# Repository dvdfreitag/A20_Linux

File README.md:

# A20_Linux
Allwinner A20-powered Linux server

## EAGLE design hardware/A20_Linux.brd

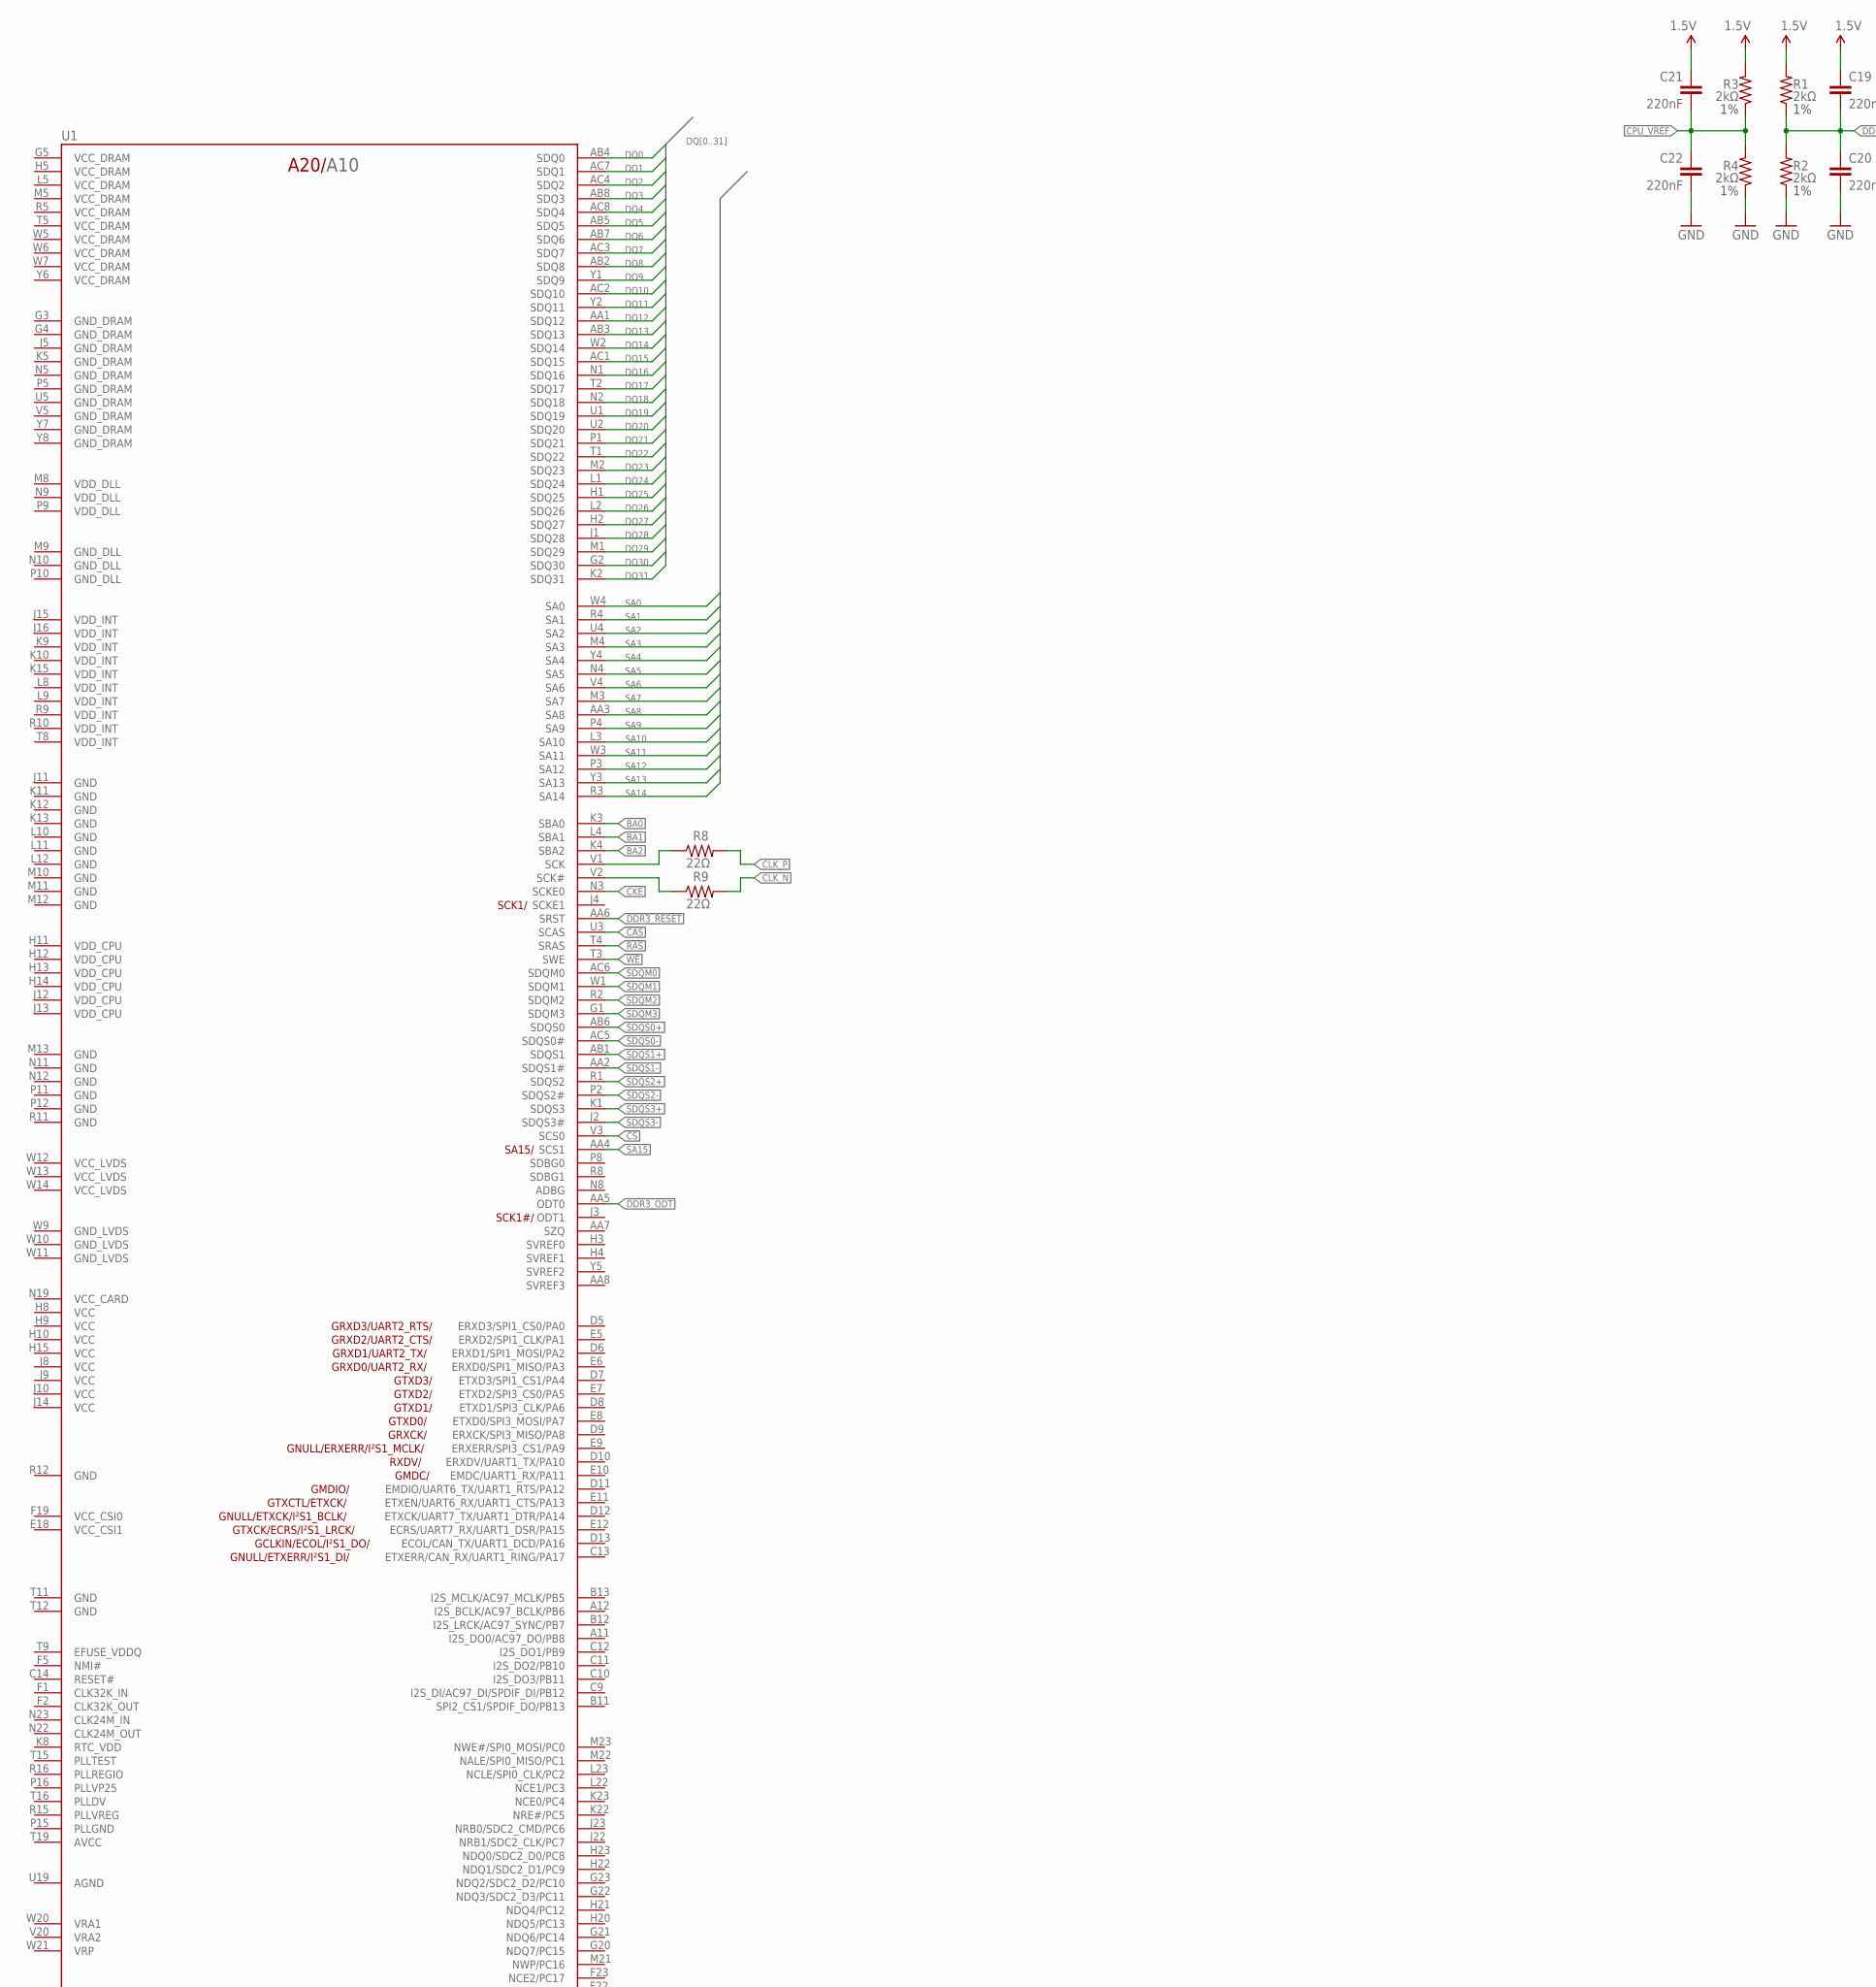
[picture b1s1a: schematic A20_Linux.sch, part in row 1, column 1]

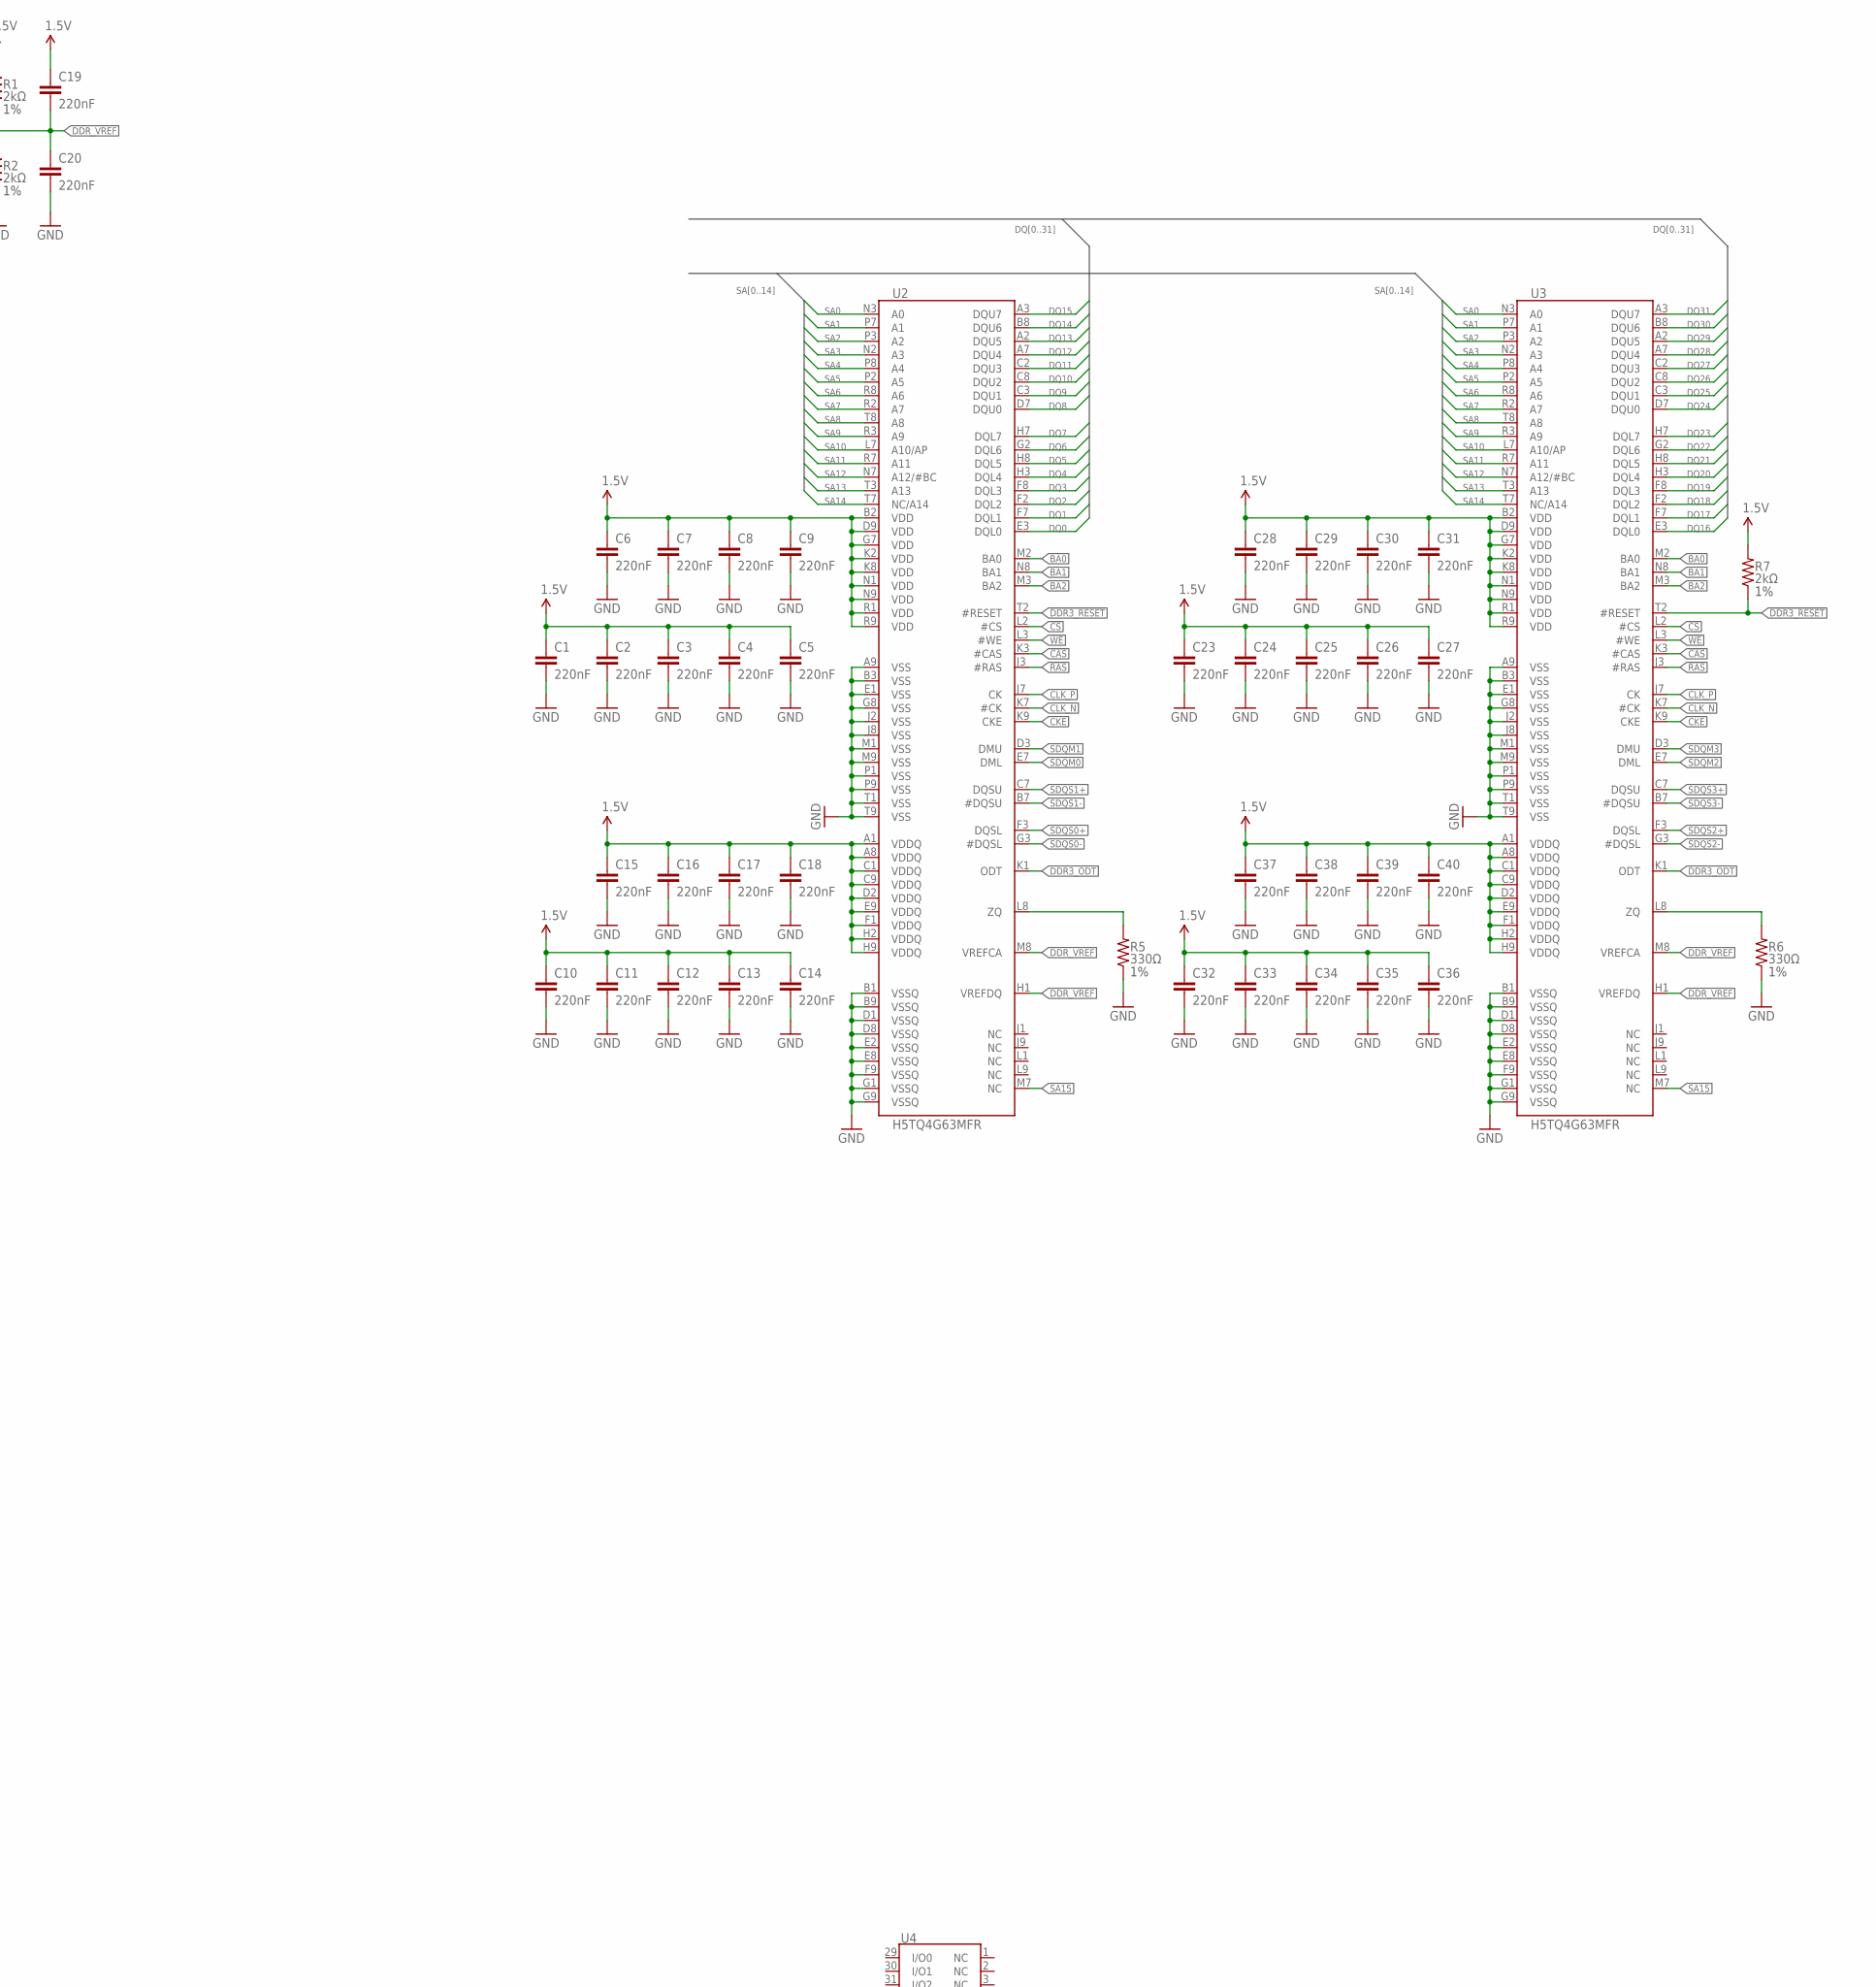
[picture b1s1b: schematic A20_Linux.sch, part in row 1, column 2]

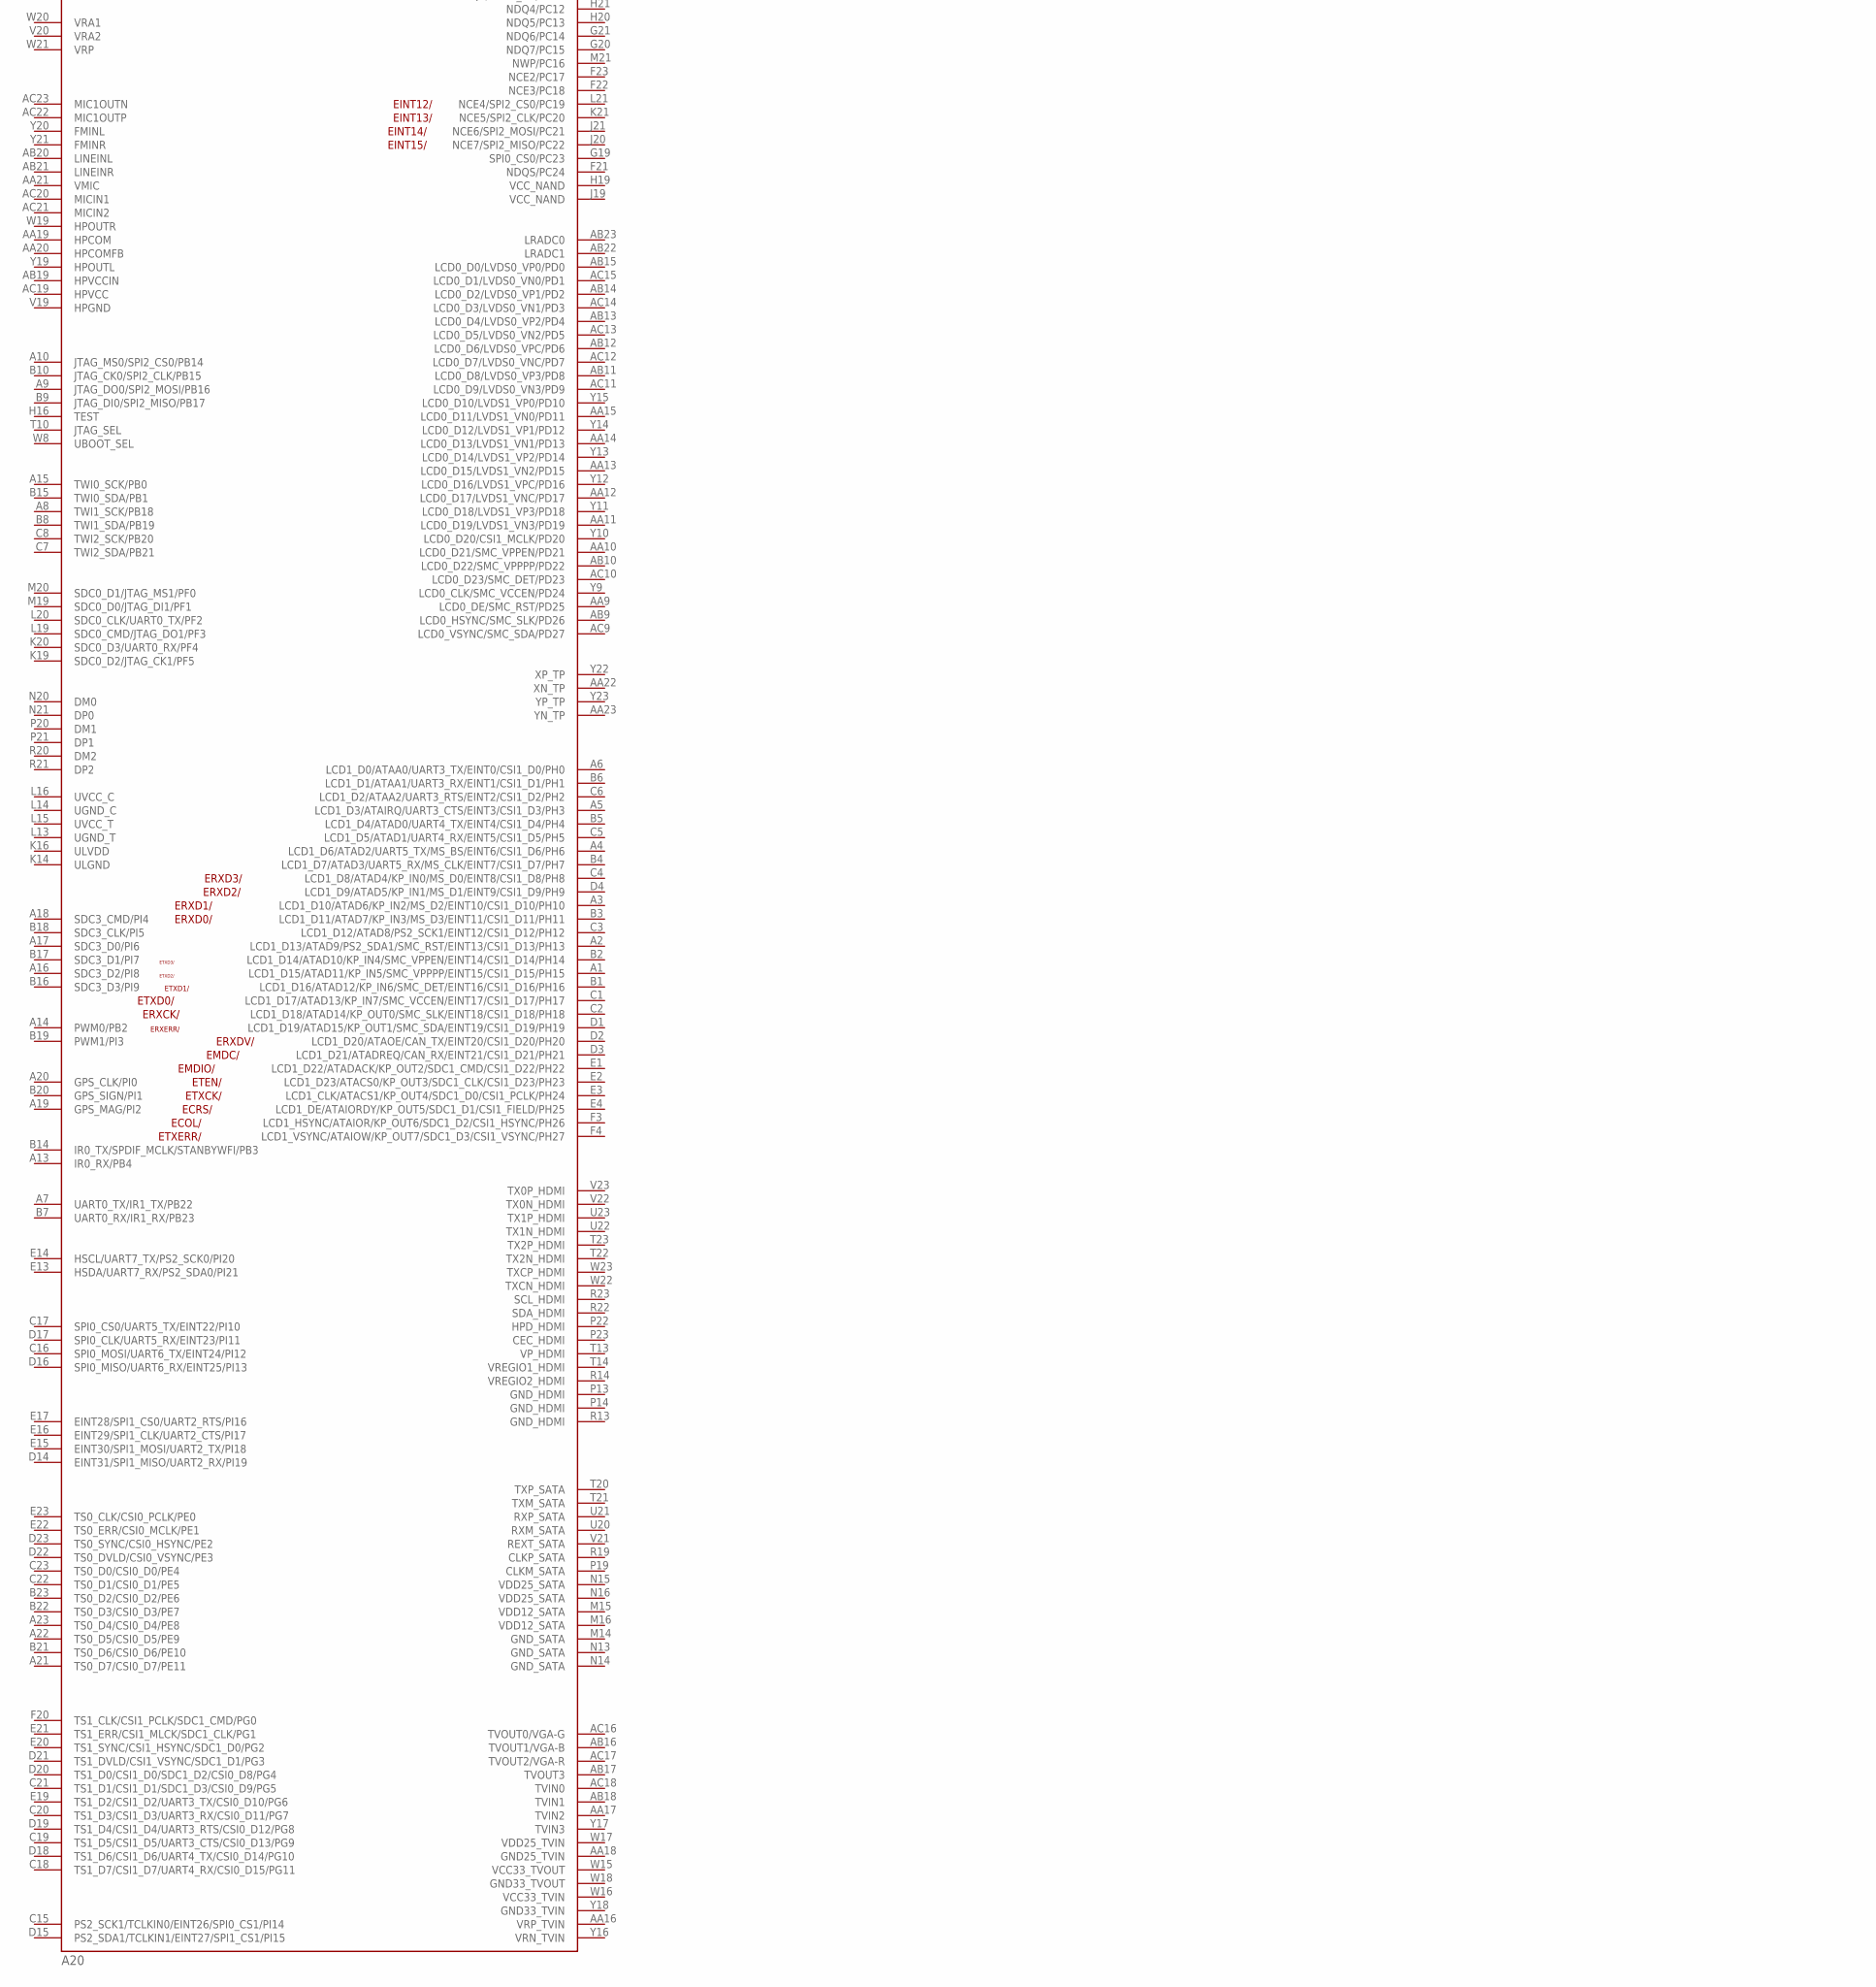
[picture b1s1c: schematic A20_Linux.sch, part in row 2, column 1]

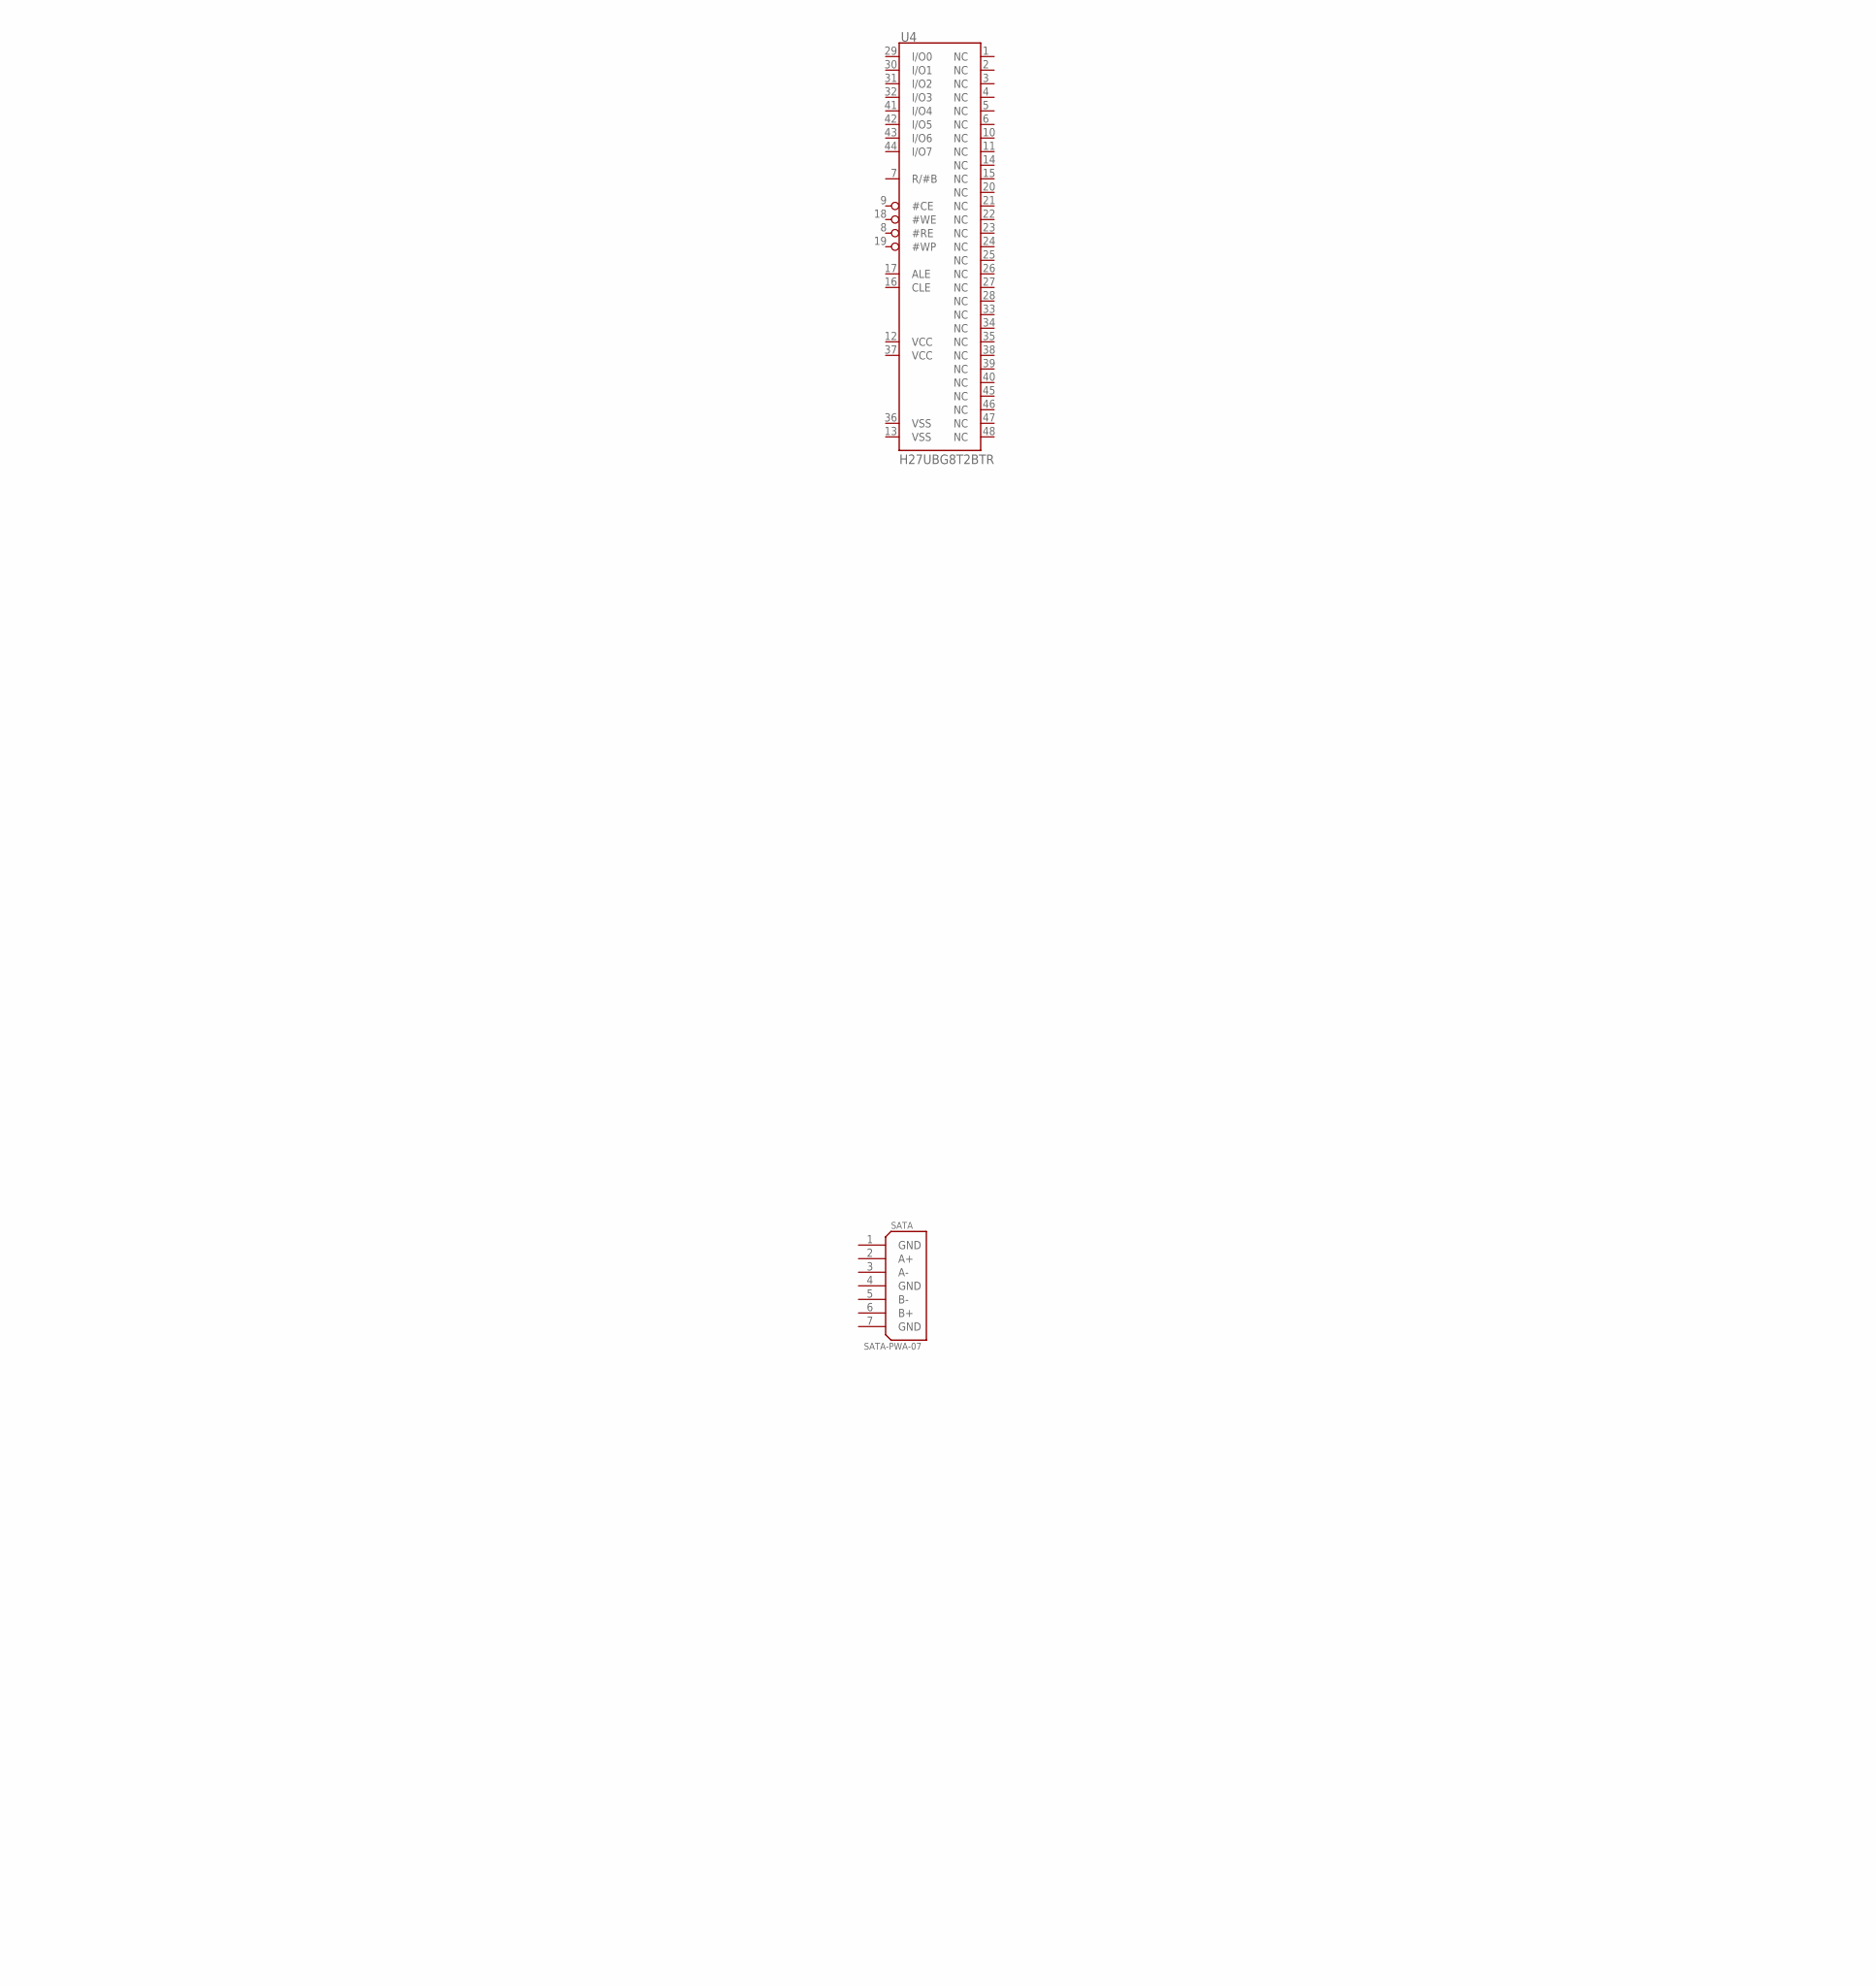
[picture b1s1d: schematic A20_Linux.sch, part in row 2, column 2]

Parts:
C1, C2, C3, C4, C5, C6, C7, C8, C9, C10, C11, C12, C13, C14, C15, C16, C17, C18, C19, C20, C21, C22, C23, C24, C25, C26, C27, C28, C29, C30, C31, C32, C33, C34, C35, C36, C37, C38, C39, C40: 220nF; 0805
R1, R2, R3, R4, R7: 2kΩ; 0805
R5, R6: 330Ω; 0805
R8, R9: 22Ω; 0402-RES
SATA: SATA-PWA-07
U1: A20; TFBGA441
U2, U3: H5TQ4G63MFR; FBGA96_SK
U4: H27UBG8T2BTR; TSOP48

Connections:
1.5V: C1.1, C2.1, C3.1, C4.1, C5.1, C6.1, C7.1, C8.1, C9.1, C10.1, C11.1, C12.1, C13.1, C14.1, C15.1, C16.1, C17.1, C18.1, C19.1, C21.1, C23.1, C24.1, C25.1, C26.1, C27.1, C28.1, C29.1, C30.1, C31.1, C32.1, C33.1, C34.1, C35.1, C36.1, C37.1, C38.1, C39.1, C40.1, R1.2, R3.2, R7.2, U2.A1 (VDDQ), U2.A8 (VDDQ), U2.B2 (VDD), U2.C1 (VDDQ), U2.C9 (VDDQ), U2.D2 (VDDQ), U2.D9 (VDD), U2.E9 (VDDQ), U2.F1 (VDDQ), U2.G7 (VDD), U2.H2 (VDDQ), U2.H9 (VDDQ), U2.K2 (VDD), U2.K8 (VDD), U2.N1 (VDD), U2.N9 (VDD), U2.R1 (VDD), U2.R9 (VDD), U3.A1 (VDDQ), U3.A8 (VDDQ), U3.B2 (VDD), U3.C1 (VDDQ), U3.C9 (VDDQ), U3.D2 (VDDQ), U3.D9 (VDD), U3.E9 (VDDQ), U3.F1 (VDDQ), U3.G7 (VDD), U3.H2 (VDDQ), U3.H9 (VDDQ), U3.K2 (VDD), U3.K8 (VDD), U3.N1 (VDD), U3.N9 (VDD), U3.R1 (VDD), U3.R9 (VDD)
!CAS: U1.U3 (SCAS), U2.K3 (#CAS), U3.K3 (#CAS)
!CS: U1.V3 (SCS0), U2.L2 (#CS), U3.L2 (#CS)
!DDR3_RESET: R7.1, U1.AA6 (SRST), U2.T2 (#RESET), U3.T2 (#RESET)
!RAS: U1.T4 (SRAS), U2.J3 (#RAS), U3.J3 (#RAS)
!WE: U1.T3 (SWE), U2.L3 (#WE), U3.L3 (#WE)
BA0: U1.K3 (SBA0), U2.M2 (BA0), U3.M2 (BA0)
BA1: U1.L4 (SBA1), U2.N8 (BA1), U3.N8 (BA1)
BA2: U1.K4 (SBA2), U2.M3 (BA2), U3.M3 (BA2)
CKE: U1.N3 (SCKE0), U2.K9 (CKE), U3.K9 (CKE)
CLK_N: R9.2, U2.K7 (#CK), U3.K7 (#CK)
CLK_P: R8.2, U2.J7 (CK), U3.J7 (CK)
CPU_VREF: C21.2, C22.1, R3.1, R4.2
DDR3_ODT: U1.AA5 (ODT0), U2.K1 (ODT), U3.K1 (ODT)
DDR_VREF: C19.2, C20.1, R1.1, R2.2, U2.H1 (VREFDQ), U2.M8 (VREFCA), U3.H1 (VREFDQ), U3.M8 (VREFCA)
DQ0: U1.AB4 (SDQ0), U2.E3 (DQL0)
DQ1: U1.AC7 (SDQ1), U2.F7 (DQL1)
DQ2: U1.AC4 (SDQ2), U2.F2 (DQL2)
DQ3: U1.AB8 (SDQ3), U2.F8 (DQL3)
DQ4: U1.AC8 (SDQ4), U2.H3 (DQL4)
DQ5: U1.AB5 (SDQ5), U2.H8 (DQL5)
DQ6: U1.AB7 (SDQ6), U2.G2 (DQL6)
DQ7: U1.AC3 (SDQ7), U2.H7 (DQL7)
DQ8: U1.AB2 (SDQ8), U2.D7 (DQU0)
DQ9: U1.Y1 (SDQ9), U2.C3 (DQU1)
DQ10: U1.AC2 (SDQ10), U2.C8 (DQU2)
DQ11: U1.Y2 (SDQ11), U2.C2 (DQU3)
DQ12: U1.AA1 (SDQ12), U2.A7 (DQU4)
DQ13: U1.AB3 (SDQ13), U2.A2 (DQU5)
DQ14: U1.W2 (SDQ14), U2.B8 (DQU6)
DQ15: U1.AC1 (SDQ15), U2.A3 (DQU7)
DQ16: U1.N1 (SDQ16), U3.E3 (DQL0)
DQ17: U1.T2 (SDQ17), U3.F7 (DQL1)
DQ18: U1.N2 (SDQ18), U3.F2 (DQL2)
DQ19: U1.U1 (SDQ19), U3.F8 (DQL3)
DQ20: U1.U2 (SDQ20), U3.H3 (DQL4)
DQ21: U1.P1 (SDQ21), U3.H8 (DQL5)
DQ22: U1.T1 (SDQ22), U3.G2 (DQL6)
DQ23: U1.M2 (SDQ23), U3.H7 (DQL7)
DQ24: U1.L1 (SDQ24), U3.D7 (DQU0)
DQ25: U1.H1 (SDQ25), U3.C3 (DQU1)
DQ26: U1.L2 (SDQ26), U3.C8 (DQU2)
DQ27: U1.H2 (SDQ27), U3.C2 (DQU3)
DQ28: U1.J1 (SDQ28), U3.A7 (DQU4)
DQ29: U1.M1 (SDQ29), U3.A2 (DQU5)
DQ30: U1.G2 (SDQ30), U3.B8 (DQU6)
DQ31: U1.K2 (SDQ31), U3.A3 (DQU7)
GND: C1.2, C2.2, C3.2, C4.2, C5.2, C6.2, C7.2, C8.2, C9.2, C10.2, C11.2, C12.2, C13.2, C14.2, C15.2, C16.2, C17.2, C18.2, C20.2, C22.2, C23.2, C24.2, C25.2, C26.2, C27.2, C28.2, C29.2, C30.2, C31.2, C32.2, C33.2, C34.2, C35.2, C36.2, C37.2, C38.2, C39.2, C40.2, R2.1, R4.1, R5.1, R6.1, SATA.1 (GND), SATA.4 (GND), SATA.7 (GND), U2.A9 (VSS), U2.B1 (VSSQ), U2.B3 (VSS), U2.B9 (VSSQ), U2.D1 (VSSQ), U2.D8 (VSSQ), U2.E1 (VSS), U2.E2 (VSSQ), U2.E8 (VSSQ), U2.F9 (VSSQ), U2.G1 (VSSQ), U2.G8 (VSS), U2.G9 (VSSQ), U2.J2 (VSS), U2.J8 (VSS), U2.M1 (VSS), U2.M9 (VSS), U2.P1 (VSS), U2.P9 (VSS), U2.T1 (VSS), U2.T9 (VSS), U3.A9 (VSS), U3.B1 (VSSQ), U3.B3 (VSS), U3.B9 (VSSQ), U3.D1 (VSSQ), U3.D8 (VSSQ), U3.E1 (VSS), U3.E2 (VSSQ), U3.E8 (VSSQ), U3.F9 (VSSQ), U3.G1 (VSSQ), U3.G8 (VSS), U3.G9 (VSSQ), U3.J2 (VSS), U3.J8 (VSS), U3.M1 (VSS), U3.M9 (VSS), U3.P1 (VSS), U3.P9 (VSS), U3.T1 (VSS), U3.T9 (VSS)
unnamed: R5.2, U2.L8 (ZQ)
unnamed: R6.2, U3.L8 (ZQ)
SA0: U1.W4 (SA0), U2.N3 (A0), U3.N3 (A0)
SA1: U1.R4 (SA1), U2.P7 (A1), U3.P7 (A1)
SA2: U1.U4 (SA2), U2.P3 (A2), U3.P3 (A2)
SA3: U1.M4 (SA3), U2.N2 (A3), U3.N2 (A3)
SA4: U1.Y4 (SA4), U2.P8 (A4), U3.P8 (A4)
SA5: U1.N4 (SA5), U2.P2 (A5), U3.P2 (A5)
SA6: U1.V4 (SA6), U2.R8 (A6), U3.R8 (A6)
SA7: U1.M3 (SA7), U2.R2 (A7), U3.R2 (A7)
SA8: U1.AA3 (SA8), U2.T8 (A8), U3.T8 (A8)
SA9: U1.P4 (SA9), U2.R3 (A9), U3.R3 (A9)
SA10: U1.L3 (SA10), U2.L7 (A10/AP), U3.L7 (A10/AP)
SA11: U1.W3 (SA11), U2.R7 (A11), U3.R7 (A11)
SA12: U1.P3 (SA12), U2.N7 (A12/#BC), U3.N7 (A12/#BC)
SA13: U1.Y3 (SA13), U2.T3 (A13), U3.T3 (A13)
SA14: U1.R3 (SA14), U2.T7 (NC/A14), U3.T7 (NC/A14)
SA15: U1.AA4 (SCS1), U2.M7 (NC), U3.M7 (NC)
SDQM0: U1.AC6 (SDQM0), U2.E7 (DML)
SDQM1: U1.W1 (SDQM1), U2.D3 (DMU)
SDQM2: U1.R2 (SDQM2), U3.E7 (DML)
SDQM3: U1.G1 (SDQM3), U3.D3 (DMU)
SDQS0+: U1.AB6 (SDQS0), U2.F3 (DQSL)
SDQS0-: U1.AC5 (SDQS0#), U2.G3 (#DQSL)
SDQS1+: U1.AB1 (SDQS1), U2.C7 (DQSU)
SDQS1-: U1.AA2 (SDQS1#), U2.B7 (#DQSU)
SDQS2+: U1.R1 (SDQS2), U3.F3 (DQSL)
SDQS2-: U1.P2 (SDQS2#), U3.G3 (#DQSL)
SDQS3+: U1.K1 (SDQS3), U3.C7 (DQSU)
SDQS3-: U1.J2 (SDQS3#), U3.B7 (#DQSU)
VCC: U4.12 (VCC), U4.37 (VCC)
VSS: U4.13 (VSS), U4.36 (VSS)
_CLK_N: R9.1, U1.V2 (SCK#)
_CLK_P: R8.1, U1.V1 (SCK)

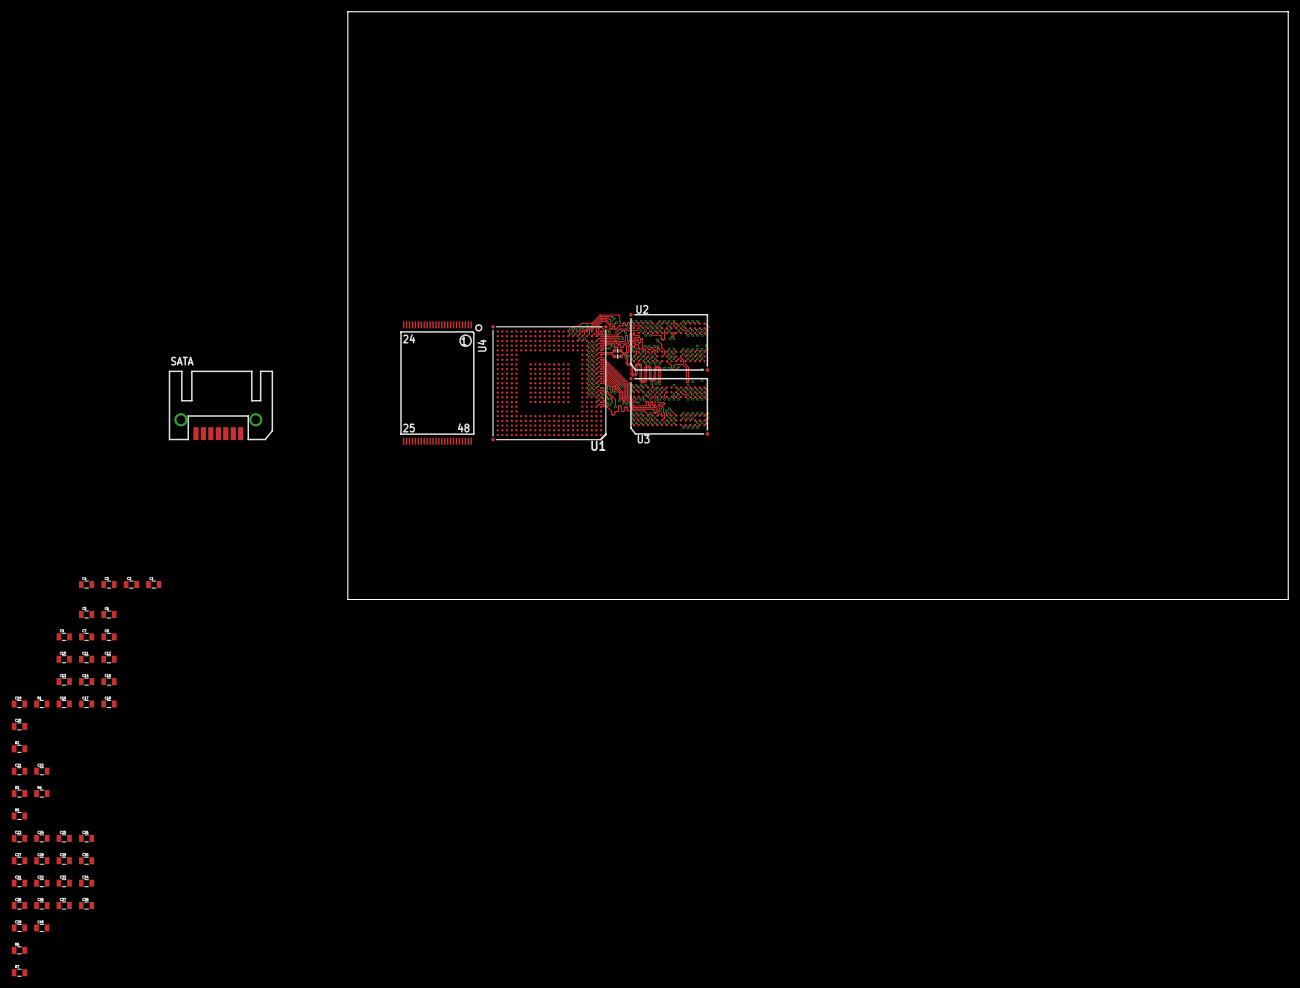
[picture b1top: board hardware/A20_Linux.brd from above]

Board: 4 copper layers, 160.0 x 100.0 mm, 54 parts (0 on the bottom side), 82 nets.

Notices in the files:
parts and their libraries:
SparkFun-Passives: Licensing: CC v3.0 Share-Alike You are welcome to use this library for commercial purposes.
